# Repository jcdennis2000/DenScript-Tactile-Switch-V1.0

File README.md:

# DenScript-Tactile-Switch-V1.0

The DenScript Tactile Switch is a standard normally open push switch in a convenient package that allows it to be easily attached to projects, with our DenScript colour coded headers to make wiring far easier! Simply connect the RED pin to positive voltage (VCC), the BLACK pin to negative voltage (GND) and the GREEN pin to an input pin on your micro controller or development board!

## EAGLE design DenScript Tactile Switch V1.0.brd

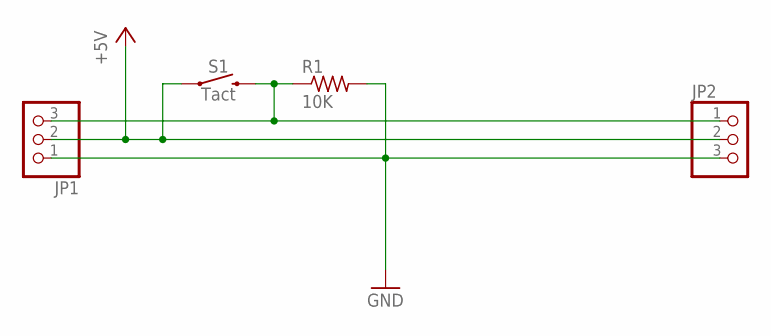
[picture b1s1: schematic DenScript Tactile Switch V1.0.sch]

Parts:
JP1, JP2: PINHD-1X3; 1X03
R1: 10K; R0603
S1: Tact; TACTILE_SWITCH_PTH_6.0MM

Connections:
+5V: JP1.2, JP2.2, S1.1
GND: JP1.1, JP2.3, R1.2
unnamed: JP1.3, JP2.1, R1.1, S1.3 (2)

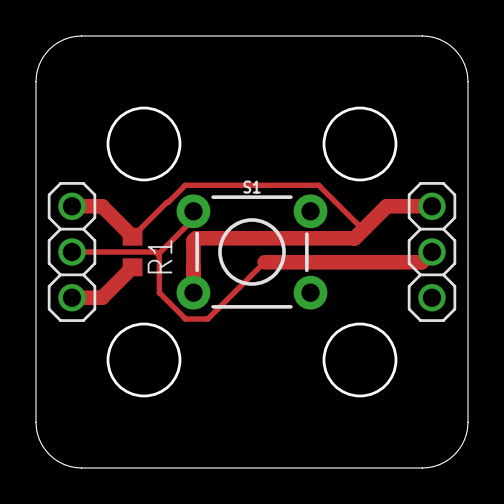
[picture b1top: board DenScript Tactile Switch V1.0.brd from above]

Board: 2 copper layers, 23.8 x 23.8 mm, 4 parts (0 on the bottom side), 3 nets.

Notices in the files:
DenScript Tactile Switch V1.0.brd:
Dennistries Ltd (c) 2019
parts and their libraries:
SparkFun-Switches: Licensing: Creative Commons ShareAlike 4.0 International - https://creativecommons.org/licenses/by-sa/4.0
